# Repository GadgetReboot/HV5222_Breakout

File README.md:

# HV5222_Breakout
HV5222 32 bit shift register breakout board
<BR><BR>
Shield: [![CC BY-SA 4.0][cc-by-sa-shield]][cc-by-sa]

This work is licensed under a
[Creative Commons Attribution-ShareAlike 4.0 International License][cc-by-sa].

[![CC BY-SA 4.0][cc-by-sa-image]][cc-by-sa]

[cc-by-sa]: http://creativecommons.org/licenses/by-sa/4.0/
[cc-by-sa-image]: https://licensebuttons.net/l/by-sa/4.0/88x31.png
[cc-by-sa-shield]: https://img.shields.io/badge/License-CC%20BY--SA%204.0-lightgrey.svg

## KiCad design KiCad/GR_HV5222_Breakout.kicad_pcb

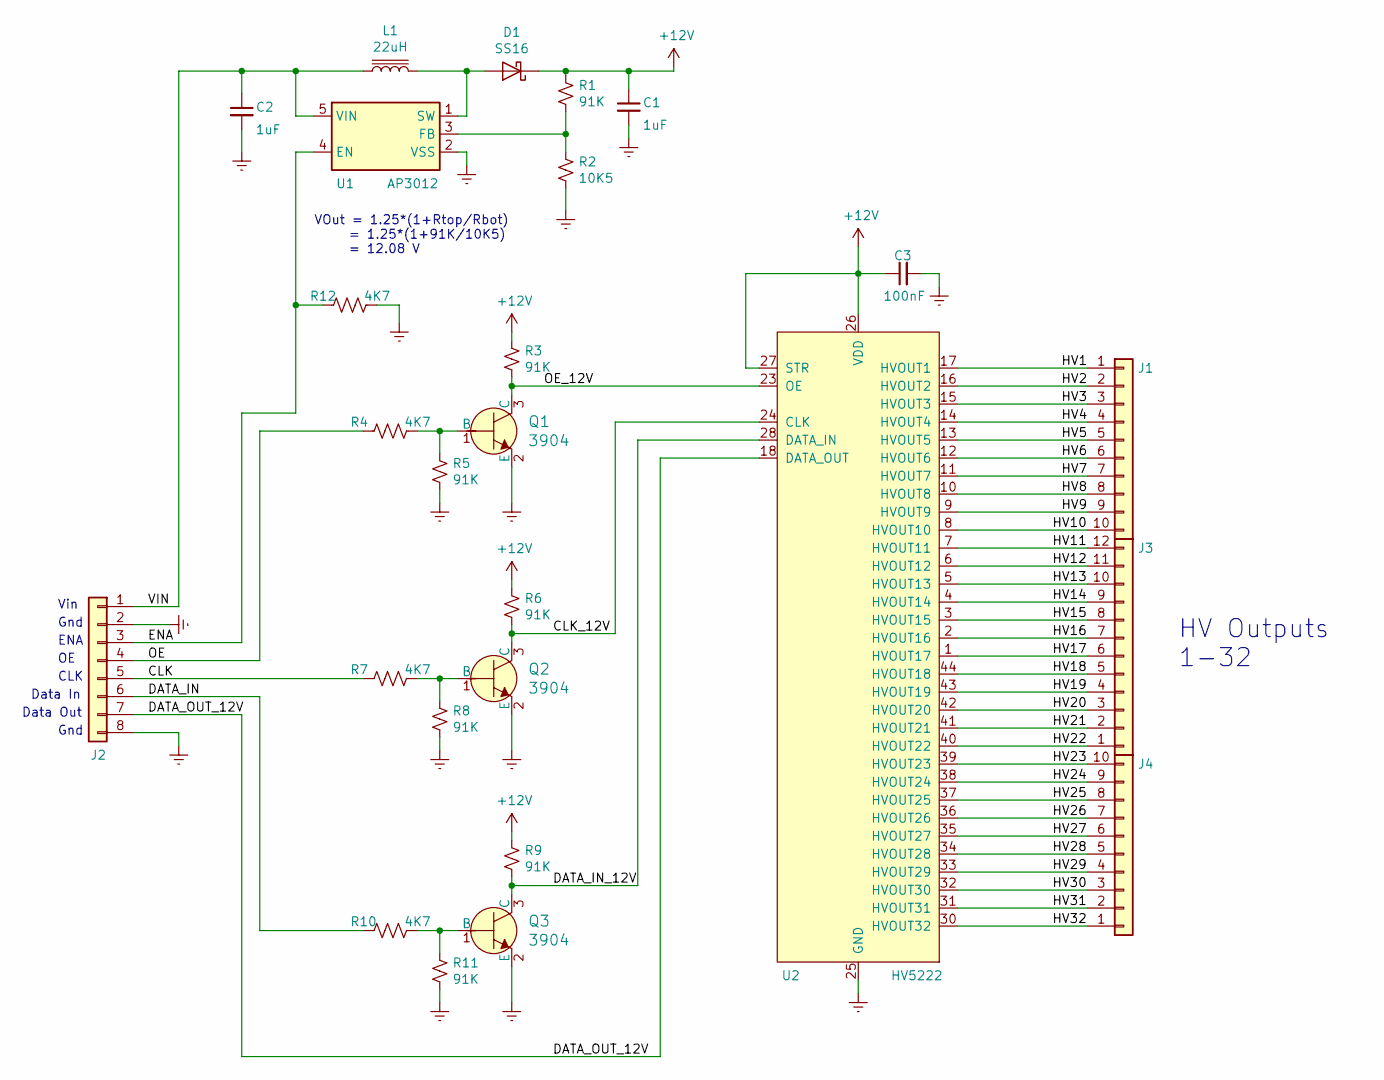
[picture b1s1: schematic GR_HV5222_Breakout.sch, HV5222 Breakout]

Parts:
C1, C2: 1uF; C_0805_2012Metric_Pad1.15x1.40mm_HandSolder; Part # CL21B105KBFNNNF
C3: 100nF; C_0805_2012Metric_Pad1.15x1.40mm_HandSolder; Part # CL21B105KBFNNNF
D1: SS16; D_SMA_Handsoldering; Part # SS16
J1, J4: Conn_01x10; PinHeader_1x10_P2.54mm_Vertical
J2: Conn_01x08; PinHeader_1x08_P2.54mm_Vertical
J3: Conn_01x12; PinHeader_1x12_P2.54mm_Vertical
L1: 22uH; L_Taiyo-Yuden_NR-60xx_HandSoldering; Part # NR6045T220M
Q1, Q2, Q3: 3904; SOT-23-3; MPN MMBT3904-TP; Digi-Key_PN MMBT3904TPMSCT-ND
R1, R3, R5, R6, R8, R9, R11: 91K; R_0805_2012Metric_Pad1.15x1.40mm_HandSolder
R2: 10K5; R_0805_2012Metric_Pad1.15x1.40mm_HandSolder
R4, R7, R10, R12: 4K7; R_0805_2012Metric_Pad1.15x1.40mm_HandSolder
U1: AP3012; SOT-23-5_HandSoldering
U2: HV5222; PLCC-44_16.6x16.6mm_P1.27mm

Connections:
+12V: C1.1, C3.1, D1.1 (K), R1.2, R3.2, R6.2, R9.2, U2.26 (VDD), U2.27 (STR)
/CLK: J2.5, R7.2
/CLK_12V: Q2.3 (C), R6.1, U2.24 (CLK)
/DATA_IN: J2.6, R10.2
/DATA_IN_12V: Q3.3 (C), R9.1, U2.28 (DATA_IN)
/DATA_OUT_12V: J2.7, U2.18 (DATA_OUT)
/ENA: J2.3, R12.2, U1.4 (EN)
/HV1: J1.1, U2.17 (HVOUT1)
/HV2: J1.2, U2.16 (HVOUT2)
/HV3: J1.3, U2.15 (HVOUT3)
/HV4: J1.4, U2.14 (HVOUT4)
/HV5: J1.5, U2.13 (HVOUT5)
/HV6: J1.6, U2.12 (HVOUT6)
/HV7: J1.7, U2.11 (HVOUT7)
/HV8: J1.8, U2.10 (HVOUT8)
/HV9: J1.9, U2.9 (HVOUT9)
/HV10: J1.10, U2.8 (HVOUT10)
/HV11: J3.12, U2.7 (HVOUT11)
/HV12: J3.11, U2.6 (HVOUT12)
/HV13: J3.10, U2.5 (HVOUT13)
/HV14: J3.9, U2.4 (HVOUT14)
/HV15: J3.8, U2.3 (HVOUT15)
/HV16: J3.7, U2.2 (HVOUT16)
/HV17: J3.6, U2.1 (HVOUT17)
/HV18: J3.5, U2.44 (HVOUT18)
/HV19: J3.4, U2.43 (HVOUT19)
/HV20: J3.3, U2.42 (HVOUT20)
/HV21: J3.2, U2.41 (HVOUT21)
/HV22: J3.1, U2.40 (HVOUT22)
/HV23: J4.10, U2.39 (HVOUT23)
/HV24: J4.9, U2.38 (HVOUT24)
/HV25: J4.8, U2.37 (HVOUT25)
/HV26: J4.7, U2.36 (HVOUT26)
/HV27: J4.6, U2.35 (HVOUT27)
/HV28: J4.5, U2.34 (HVOUT28)
/HV29: J4.4, U2.33 (HVOUT29)
/HV30: J4.3, U2.32 (HVOUT30)
/HV31: J4.2, U2.31 (HVOUT31)
/HV32: J4.1, U2.30 (HVOUT32)
/OE: J2.4, R4.2
/OE_12V: Q1.3 (C), R3.1, U2.23 (OE)
/VIN: C2.1, J2.1, L1.1, U1.5 (VIN)
GNDREF: C1.2, C2.2, C3.2, J2.2, J2.8, Q1.2 (E), Q2.2 (E), Q3.2 (E), R2.1, R5.1, R8.1, R11.1, R12.1, U1.2 (VSS), U2.25 (GND)
unnamed: D1.2 (A), L1.2, U1.1 (SW)
unnamed: Q1.1 (B), R4.1, R5.2
unnamed: Q2.1 (B), R7.1, R8.2
unnamed: Q3.1 (B), R10.1, R11.2
unnamed: R1.1, R2.2, U1.3 (FB)

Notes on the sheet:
VOut = 1.25*(1+Rtop/Rbot) = 1.25*(1+91K/10K5) = 12.08 V
Vin
Gnd
CLK
Data In
Data Out
HV Outputs 1-32
ENA

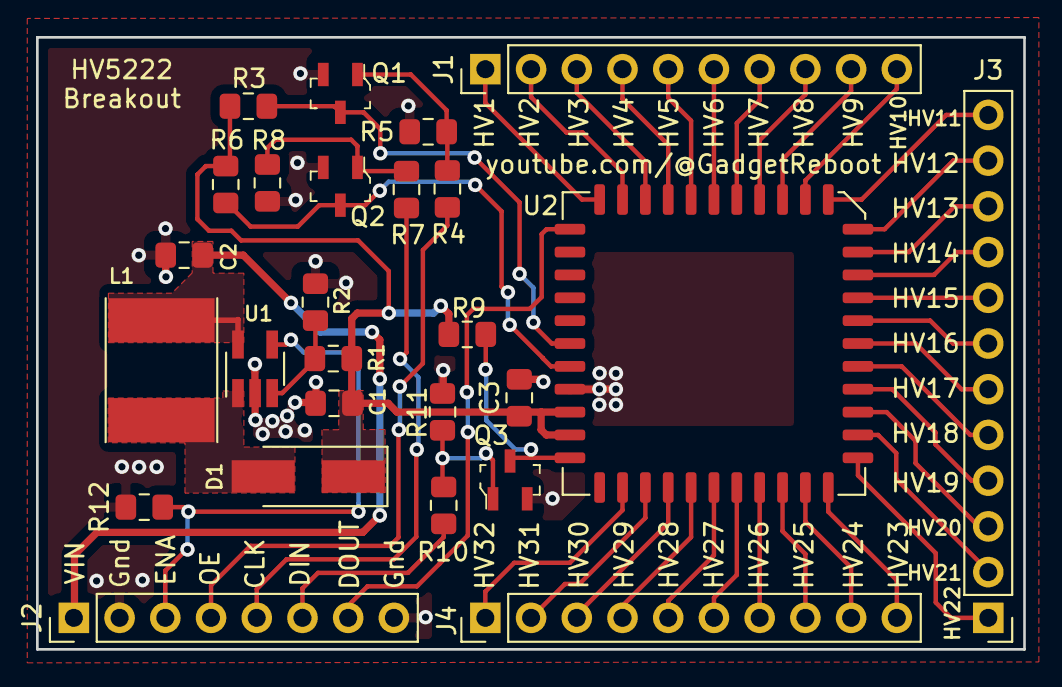
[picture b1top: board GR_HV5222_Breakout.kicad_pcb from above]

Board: 2 copper layers, 54.8 x 34.0 mm, 26 parts (0 on the bottom side), 48 nets.

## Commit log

2024-04-20 Update LICENSE
